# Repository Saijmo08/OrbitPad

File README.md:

# OrbitPad

OrbitPad is a 12-key macropad built around a Raspberry Pi Pico. It combines two rotary encoders, a separate layer button, an external RGB LED chain, and an OLED connector with a Windows app for editing shortcuts and profiles.

> **Current status:** The keyboard and configurator code is included, but the OLED is disabled in this firmware because its physical framebuffer output has not been verified. This is a project in progress, **not** a tested manufacturing release.

## Features

- **12 configurable keys** arranged as four rows and three columns. The app numbers them **down** each column:

  ```text
   1   5   9
   2   6  10
   3   7  11
   4   8  12
  ```

- **Profiles and layers:** each profile can contain different 12-key layouts. The separate button on GP9 cycles layers.
- **Two external rotary encoders:** currently mapped to volume/mute and media playback controls.
- **12 external addressable RGB LEDs:** driven from GP19.
- **128 × 128 OLED connection:** screen-layout previews exist, but the actual display output is **not working in the current release**.
- **Windows configurator:** set a shortcut per key, then send the CSV to the pad over its USB **data** port. Saving also remembers the selected profile for the next boot.

## CAD Model

The complete assembly is [`cad/Macro Pad Case.step`](cad/Macro%20Pad%20Case.step); its STEP model contains the enclosure, PCB and Pico models. The printable parts are [`Top.step`, `Bottom.step`, `Button.step`, and `Button Stick.step`](production/board/hardware/).

## PCB

The editable design is in [`pcb/`](pcb/): [`Macro Pad.kicad_pro`](pcb/Macro%20Pad.kicad_pro), [`Macro Pad.kicad_sch`](pcb/Macro%20Pad.kicad_sch), and [`Macro Pad.kicad_pcb`](pcb/Macro%20Pad.kicad_pcb). The current [Gerber/drill ZIP](production/board/hardware/Macro_Pad.zip) is in `production/board/hardware/`.

## Firmware Overview

The Pico runs **CircuitPython + [KMK](https://github.com/KMKfw/kmk_firmware)**. Its application is `production/board/software/code.py`; `boot.py` controls the normal USB modes. The included `.uf2` installs CircuitPython, **not** the OrbitPad app. KMK itself is in `production/board/software/kmk/` and must also be copied onto the Pico.

In the [Windows configurator](`production/Configuration App/Configuration App.exe`), **Apply** saves the local CSV and **Save on Pad** uploads it. Only the **Shortcut** field sends a keystroke, therefore icons and titles are labels. GP9 changes layers, while GP15 reveals `CIRCUITPY` when held during USB plug-in. On reboot, the last saved profile starts on its first layer.

The OLED interface remains wired but `OLED_ENABLED = False` and screen uploads are off. [Installation and manufacturing details →](production/README.md)

**Software preview:**

## BOM

A parts list from the off-board connectors:

- 1 × RP2040 Raspberry Pi Pico; RPI-PICO
- 12 × CHERRY MX Blue Switches; MX1A-E1NN
- 12 × Diodes, THT, 100V, 300mA, DO35; 1N4148
- 2 × 6 mm pushbuttons
- 1 × 100 µF radial capacitor
- 1 × 1.5" 128x128 OLED display module, SPI/ I2C Interface; OLED-15W-C
- 2 × rotary encoders; KY-040-2
- 1 × NeoPixel ring with 12 WS2812 5050 RGB LEDs; NEOPR12
- 1 × Adafruit MicroUSB extencion for Panel mounting; 3258

For a more detailed list of all the parts take a look at the **BOM.csv** at `production/BOM.csv`.

## Extra stuff

The [production README](production/README.md) covers board flashing, KMK installation and connector pins.

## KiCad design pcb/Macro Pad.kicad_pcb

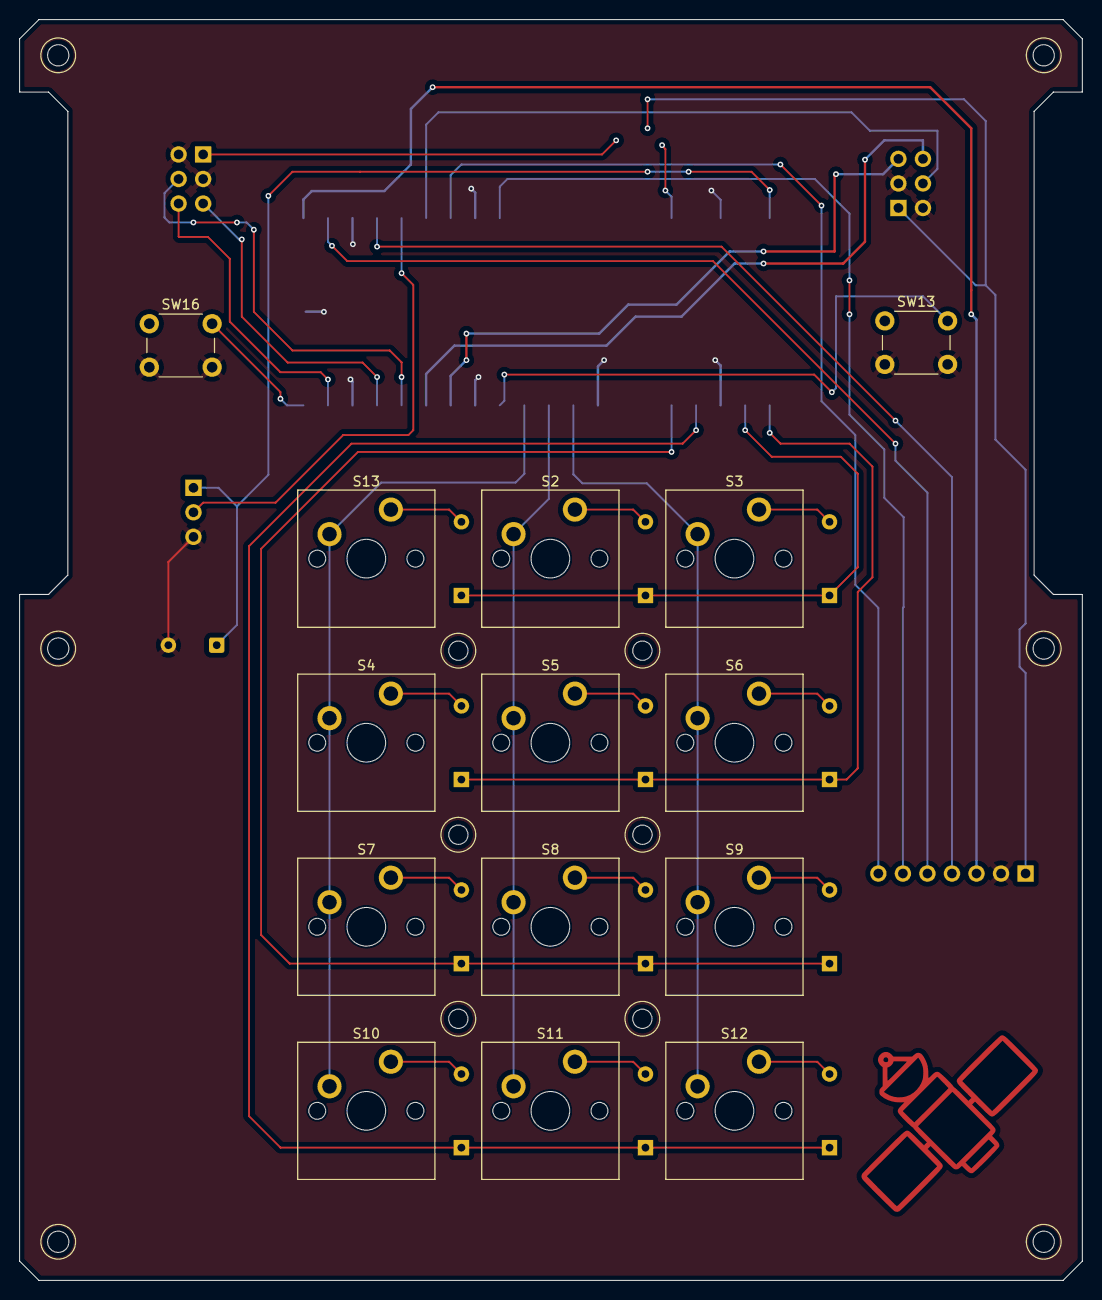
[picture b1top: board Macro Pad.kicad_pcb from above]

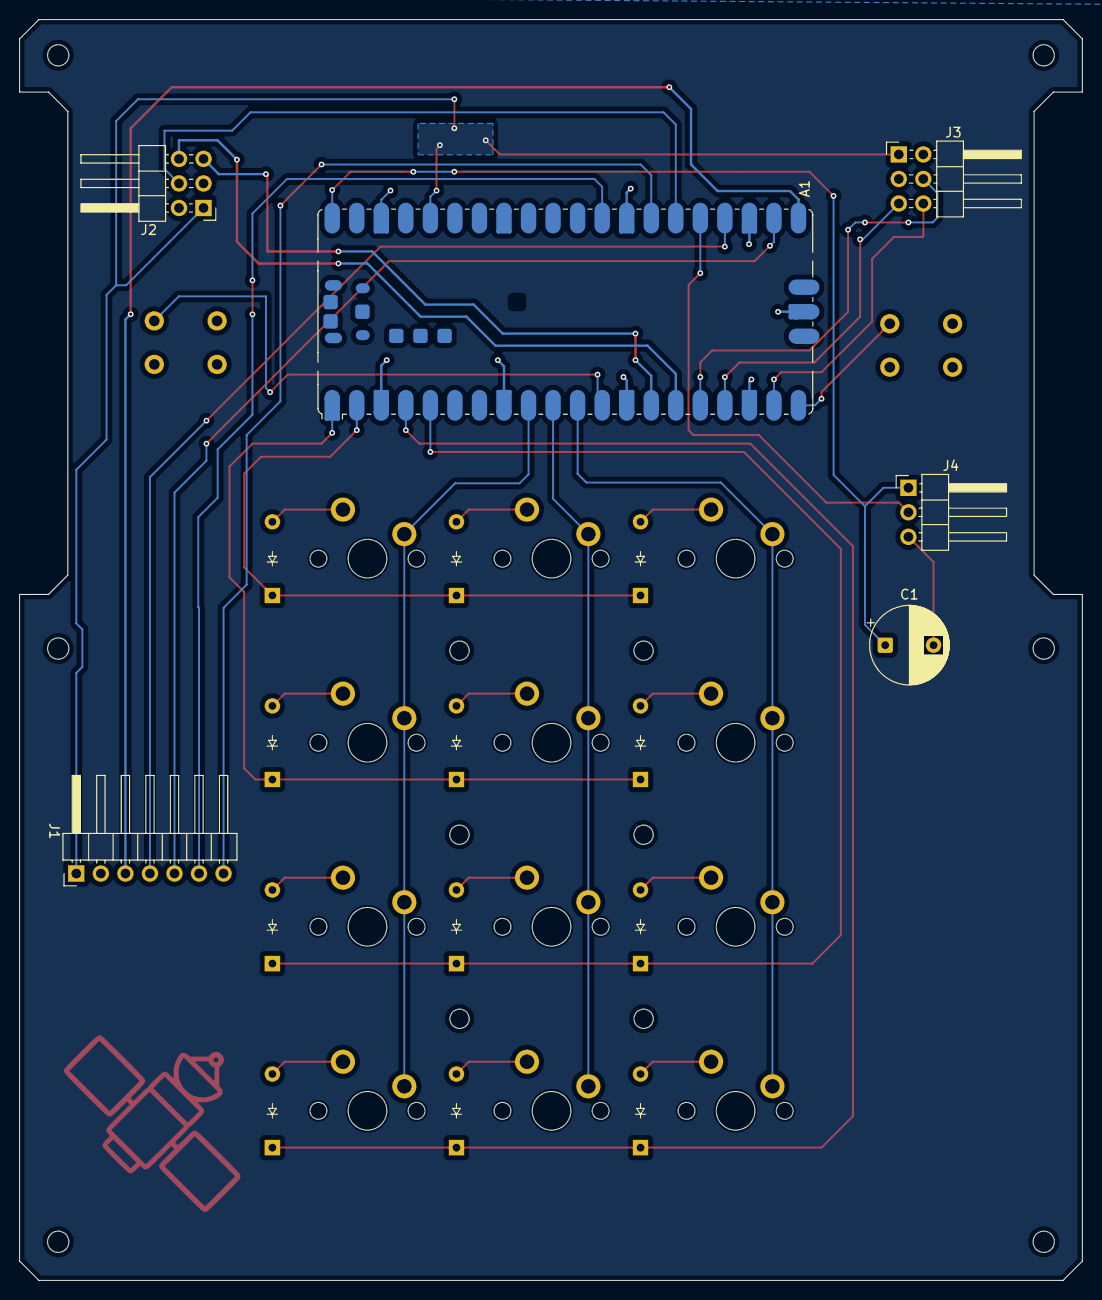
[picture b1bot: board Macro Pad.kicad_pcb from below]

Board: 2 copper layers, 110.0 x 130.5 mm, 32 parts (18 on the bottom side), 36 nets.

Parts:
A1: RaspberryPi_Pico; RaspberryPi_Pico_SMD
C1: 100µF; CP_Radial_D8.0mm_P5.00mm
D1, D2, D3, D4, D5, D6, D7, D8, D9, D10, D11, D12: Diode_DO-35
J1: OLED Screen; PinHeader_1x07_P2.54mm_Horizontal
J2, J3: Conn_01x06_MountingPin; PinHeader_2x03_P2.54mm_Horizontal
J4: Conn_01x03_Pin; PinHeader_1x03_P2.54mm_Horizontal
S2, S3, S4, S5, S6, S7, S8, S9, S10, S11, S12, S13: MX_PCB_1.00u
SW13, SW16: SW_Push_Dual; SW_PUSH_6mm

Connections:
+3.3V: A1.36 (3V3), J1.1, J2.1, J3.1
/9: A1.12 (GPIO9), SW13.1
/10: A1.14 (GPIO10), J2.5
/11: A1.15 (GPIO11), J2.6
/12: A1.16 (GPIO12), J3.4
/13: A1.17 (GPIO13), J3.5
/14: A1.19 (GPIO14), J3.6
/15: A1.20 (GPIO15), SW16.1
/20: A1.26 (GPIO20), J2.4
Col 0: A1.11 (GPIO8), S4.1, S7.1, S10.1, S13.1
Col 1: A1.10 (GPIO7), S2.1, S5.1, S8.1, S11.1
Col 2: A1.9 (GPIO6), S3.1, S6.1, S9.1, S12.1
GND: A1.3 (GND), A1.8 (GND), A1.13 (GND), A1.18 (GND), A1.23 (GND), A1.28 (GND), A1.38 (GND), A1.D2 (GND), C1.2, J1.2, J2.2, J2.3, J3.2, J3.3, J4.3, SW13.2, SW16.2
unnamed: A1.21 (GPIO16), J1.3
unnamed: A1.22 (GPIO17), J1.5
unnamed: A1.24 (GPIO18), J1.4
unnamed: A1.25 (GPIO19), J4.2
unnamed: A1.27 (GPIO21), J1.7
unnamed: A1.29 (GPIO22), J1.6
unnamed: A1.40 (VBUS), C1.1, J4.1
unnamed: D1.2 (A), S2.2
unnamed: D2.2 (A), S3.2
unnamed: D3.2 (A), S4.2
unnamed: D4.2 (A), S5.2
unnamed: D5.2 (A), S6.2
unnamed: D6.2 (A), S7.2
unnamed: D7.2 (A), S8.2
unnamed: D8.2 (A), S9.2
unnamed: D9.2 (A), S10.2
unnamed: D10.2 (A), S11.2
unnamed: D11.2 (A), S12.2
unnamed: D12.2 (A), S13.2
Row 0: A1.2 (GPIO1), D1.1 (K), D2.1 (K), D12.1 (K)
Row 1: A1.1 (GPIO0), D3.1 (K), D4.1 (K), D5.1 (K)
Row 2: A1.5 (GPIO3), D6.1 (K), D7.1 (K), D8.1 (K)
Row 3: A1.4 (GPIO2), D9.1 (K), D10.1 (K), D11.1 (K)
